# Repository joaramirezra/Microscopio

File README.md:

# Sistema de conteo de minerales para microscopio 

El siguiente repositorio cuenta con la informacion necesaria para ejecutar un sistema de conteo de minerales de manera semi-automatica haciendo uso de un microscopio, para ello es necesario poseer los siguientes componentes :

 - Computador con Linux,Windows o mac (Soporte unicamente para los dos primeros )
 - Carro de conteo automatico de puntos (Opcional ,Mas informacion proximente)
 - Dispositivo de comunicacion entre el carro de conteo y el PC (opcional)

El sistema de funcionamiento cuenta con una interfaz de usuario como se muestra a continuacion 

En ella podemos observar 5 secciones :

 1. Interfaz de conexion con dispositivo fisico
 2. Interfaz para agregar nuevas conbinaciones mineral y conjunto de letras
 3. Interfaz para agregar/borrar minerales al conteo.
 4. Resumen de minerales recientemente agregados
 5. Graficas del total de elementos agregados
 
Esta secciones permiten al usuario interactuar con el dispositivo fisico (si se posee) de tal manera que a medida que se van agregando minerales al conteo, estos de manera automatica se actualizan en la interfaz de usuario a medida que la seccion delgada se mueve de manera automatica 

## Instalación 

El proceso de instalaccion consiste en la correcta instalacion de las siguientes dependencias 
 - [python 3.6 o superior](https://www.python.org/downloads/)
    - [pyQT5](https://pypi.org/project/PyQt5/)
    - [pySerial](https://pyserial.readthedocs.io/en/latest/pyserial.html#installation)
  
Ademas de la  instalacion de las dependencias se recomienda utilizar un programa para detectar los puertos este puede ser :
- [Arduino](https://www.arduino.cc/en/software)
- [PuTTY](https://www.putty.org/)
- ó cualquiera a elección 

### checkeo requetimientos ( integridad instalacion )

Una vez instaladas las dependencias, entrar al directorio :

```
./pruebas/instalacion/
```

Alli encontrara el scrip llamado `test.py` , al ejecutarse debera obtener una respuesta como la siguiente : 

``` 
Dependencias correctamente instaladas
```

## Puesta en marcha (omitir este paso si no se posee el carro de secciones delgadas)

Para la correcta deteccion del puerto se recomienda seguir con los siguientes paso :
 1. Conexion previa : la conexion se debe realizar como se muestra en el siguiente diagrama

  alli se debe conectar el dispositivo a una fuente de voltaje de 120 Vac (toma corriente en Colombia), en ese instante debe encender una luz led como se muestra en la siguiente Imagen 

  Una vez conectado la alimentacion del dispositivo, se debe conectar un cable USB entre el computador y el dispositivo, este a su vez encendera una segunda luz en el dispositvo como se muestra en la siguiente imagen:

 2. Deteccion de puerto 
 
 Posterior a la conexion del dispositvo se debe identificar el puerto de conexion para sincronizar el dispositivo con el programa para ello acudimos al programa arduino, (o cualquiera de su preferencia) , alli presionamos
 
``` 
Herramientas/puertos
```
 Debera aparecer el nombre del puerto que se relaciona al dispositvo fisico que conectamos en el paso anterior como se muestra en la siguiente imagen (el nombre del puerto puede variar)

  - Nota 1 : En caso de usar linux se recomienda dar permisos de escritura y lectura al puerto mediante el comando `sudo chmod /dev/Nombre_del_puerto` 
  - Nota 2 : En caso de desconectar y reconectar el dispositivo asegurese que el nombre del puerto sea el mismo , en caso contrario se debe dar permisos a este nuevo puerto
  - Nota 3 : En caso de desconectar y reconectar el dispositivo asegurese que el nombre del puerto sea el mismo , en caso contrario actualizar el nombre en la interfaz grafica 
 
 3. Sincronizacion del dispositivo 
 
 Una vez se tiene el identificado el nombre del puerto y el dispositvo este correctamente conectado, se debe introducir el nombre del puerto en la casilla nombre y presionar sincronizar, esto debera 
  
7. Bibliografia 

## Agregar Nuevo combinacion mineral 

Una vez se ha sincronizado el carro con el programa es momento de iniciar a agregar los elementos a la lista de minerales que van a estar disponibles, para ello se se posee la siguientes restricciones

Es Sensible a combinaciones entre mayusculas y minisculas
longitud maxima  3 Letras
No soporta caracteres especiales ni numeros (estos ultimos estan reservados para hacer referencia a los tamaños)

### (Previo) Deteccion de puertos 

## something else 

# Colaboladores 

- [Johan Ramirez](https://github.com/joaramirezra)
- [Jurgen Krajcy](https://github.com/JurgenHK)
- Thomas Crammer

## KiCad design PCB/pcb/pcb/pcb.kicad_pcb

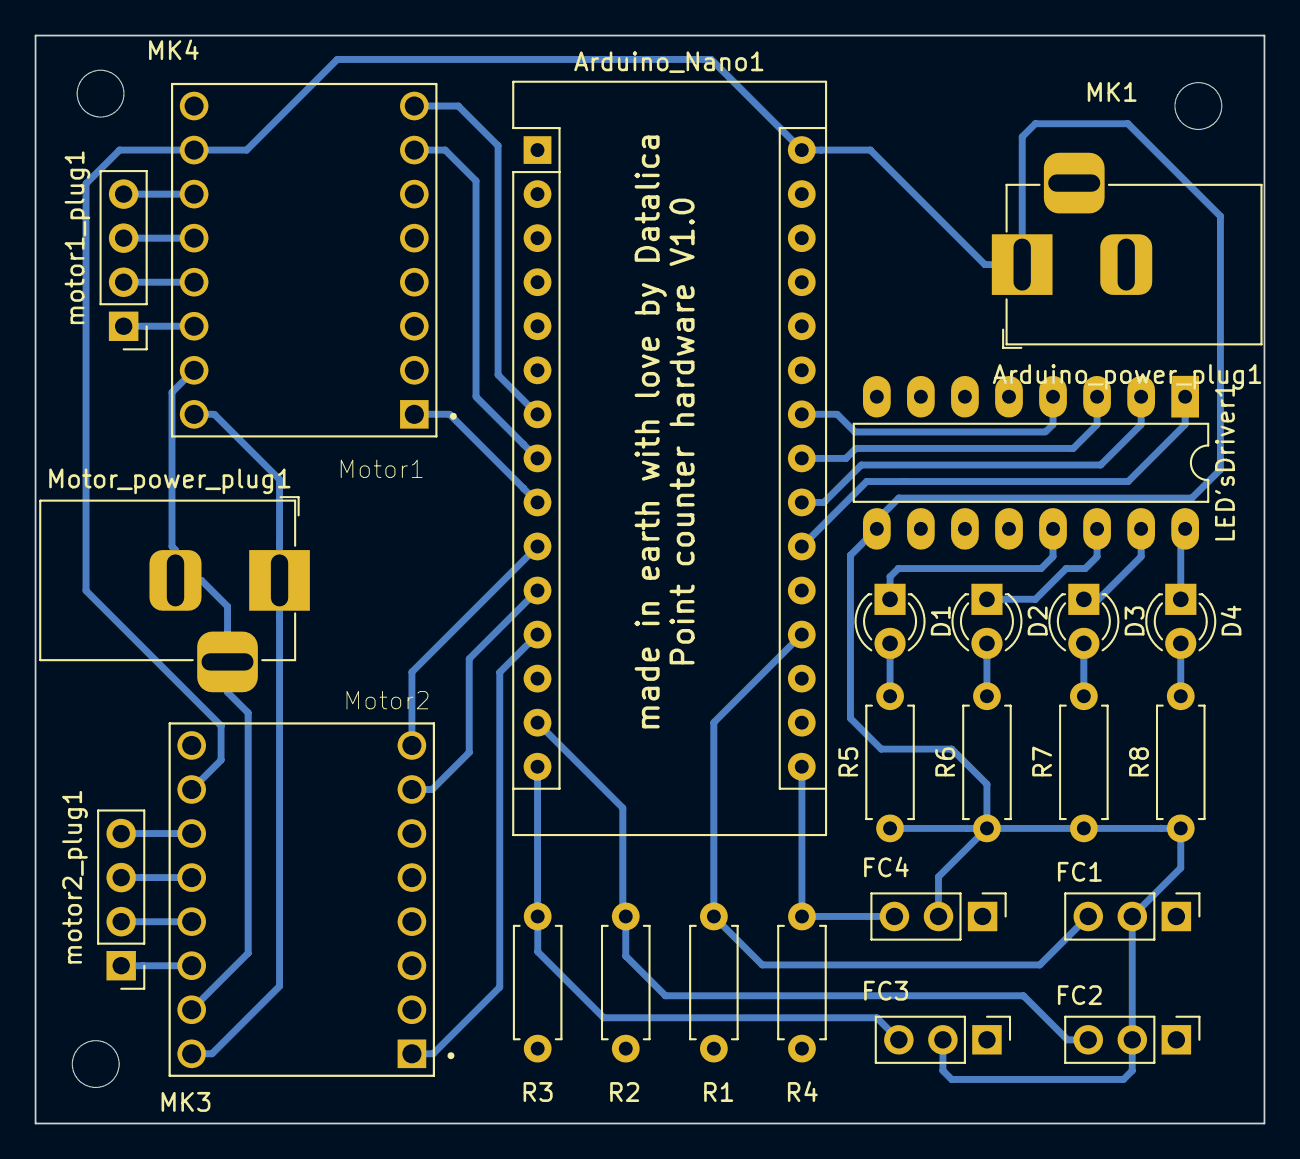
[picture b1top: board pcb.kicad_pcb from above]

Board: 2 copper layers, 70.9 x 62.7 mm, 27 parts (0 on the bottom side), 34 nets.

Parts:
Arduino_Nano1: Arduino_Nano_v2.x; Arduino_Nano
Arduino_power_plug1: Conn_01x03_Female; BarrelJack_Horizontal
D1, D2, D3, D4: LED; LED_D3.0mm_FlatTop
FC1, FC2, FC3, FC4: Conn_01x03_Female; PinHeader_1x03_P2.54mm_Vertical
LED'sDriver1: ULN2003A; DIP-16_W7.62mm_LongPads
MK1, MK3, MK4: M2.5; MountingHole_2.7mm_M2.5
Motor1, Motor2: TMC2100; IC_DRV8825_STEPPER_MOTOR_DRIVER_CARRIER
Motor_power_plug1: Conn_01x03_Female; BarrelJack_Horizontal
R1, R2, R3, R4: 10K; R_Axial_DIN0207_L6.3mm_D2.5mm_P7.62mm_Horizontal
R5, R6, R7, R8: 220; R_Axial_DIN0207_L6.3mm_D2.5mm_P7.62mm_Horizontal
motor1_plug1, motor2_plug1: Conn_01x04_Male; PinHeader_1x04_P2.54mm_Vertical

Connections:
+5V: Arduino_Nano1.30, Arduino_power_plug1.1, FC1.2, FC2.2, FC3.2, FC4.2, LED'sDriver1.9, Motor1.10, Motor2.10, R5.1, R6.1, R7.1, R8.1
Dir_motor1: Arduino_Nano1.7, Motor1.8
Dir_motor2: Arduino_Nano1.10, Motor2.8
EN_motor1: Arduino_Nano1.9, Motor1.1
EN_motor2: Arduino_Nano1.12, Motor2.1
GND: Arduino_Nano1.29, Arduino_power_plug1.2, Arduino_power_plug1.3, LED'sDriver1.8, Motor1.9, Motor2.9, R1.2, R2.2, R3.2, R4.2
GND_motor: Motor1.15, Motor2.15, Motor_power_plug1.2, Motor_power_plug1.3
LED1: Arduino_Nano1.21, LED'sDriver1.1
LED2: Arduino_Nano1.22, LED'sDriver1.2
LED3: Arduino_Nano1.23, LED'sDriver1.3
LED4: Arduino_Nano1.24, LED'sDriver1.4
Limit_switch1: Arduino_Nano1.19, FC1.3, R1.1
Limit_switch2: Arduino_Nano1.14, FC2.3, R2.1
Limit_switch3: Arduino_Nano1.15, FC3.3, R3.1
Limit_switch4: Arduino_Nano1.16, FC4.3, R4.1
unnamed: D1.2, R5.2
unnamed: D2.2, R6.2
unnamed: D3.2, R7.2
unnamed: D4.2, R8.2
S_LED1: D1.1, LED'sDriver1.13
S_LED2: D2.1, LED'sDriver1.14
S_LED3: D3.1, LED'sDriver1.15
S_LED4: D4.1, LED'sDriver1.16
Step_motor1: Arduino_Nano1.8, Motor1.7
Step_motor2: Arduino_Nano1.11, Motor2.7
Vmot_1: Motor1.16, Motor2.16, Motor_power_plug1.1
moto2_1B: Motor2.11, motor2_plug1.4
motor1_1A: Motor1.12, motor1_plug1.3
motor1_2A: Motor1.13, motor1_plug1.2
motor1_2B: Motor1.14, motor1_plug1.1
motor2_1A: Motor2.12, motor2_plug1.3
motor2_2A: Motor2.13, motor2_plug1.2
motor2_2B: Motor2.14, motor2_plug1.1
motor_1B: Motor1.11, motor1_plug1.4

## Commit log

2020-09-03 init
2020-09-03 v0.001
2020-09-04 v0.002
2020-09-06 V0.003
2020-09-07 v0.003 add class car
2020-09-07 v0.003 working on the file system control
2020-09-07 v0.003 dataflow work
2020-09-10 v0.005 interfaz optimizada
2020-09-11 V0.01 basic UI almost finish need to embed the graphs
2020-09-11 v0.005 add element
2020-09-11 v0.01 implementing dictionaries to save elements, looks to work great
2020-09-12 v01 putting the grpahs
2020-09-12 v0.02 Principal UI components working
2020-09-12 v0.02 a good day finish with all working
2020-09-13 v0.08 ux finised, also is working the add new element and is partialy the automatic counting
2020-09-14 v0.08 style working
2020-09-14 V0.09 add to table elements
2020-09-14 V0.1 element and size validation
2020-09-14 v0.15 add element to table with size
2020-09-15 v0.5 julio version
2020-09-15 v0.5 from here Julio is working in the repo
2020-09-15 New branch,Johan init
2020-09-15 V0.5 begin to work in PCB
2020-09-16 v0.6 drivers symbols created
2020-09-16 v0.6 create some milestone and fixed #1
2020-09-17 V0.7 finish the schematic that close #4
2020-09-17 V0.75 all the footprints were set
2020-09-17 V0.8 this commit close #5 also fixes #6
2020-09-17 V0.8 pcb Finished this closes #9 and closes #8
2020-09-18 V0.82 the gerbers were generated and sent to fabrication that close #7
2020-09-18 V0.85 putting bars with stepMode that is a point to solve #12
2020-09-21 V0.88 working pcb and waiting to solderin
2020-09-23 V0.86 changing color under plot line
2020-09-23 v0.9 finally put the axis labels
2020-09-23 v0.9 debug labels
2020-09-23 V0.9 code clean
2020-09-24 V 0.91 writing file line by line
2020-09-24 v0.92 point saved in a file, also the file can be reset
2020-09-24 V0.93 code to test motot
2020-09-26 V0.93 probed that code works with motors
2020-09-28 V0.93 motor with the right direr
2020-09-28 V0.94 working motor with AccelStepper library
2020-09-29 V0.94 testing comunication
2020-09-30 V0.94 motor step calculators
2020-10-01 V0.94 just some ajustments
2020-10-01 V0.95 adding 2do motor
2020-10-01 V0.95 putting switch
2020-10-02 V0.95 homing Working
2020-10-02 V0.95 serial comunication working
2020-10-02 Version 1.0
2020-10-03 V1.0 code refactor
2020-10-04 V1.01 fixing comunication
2020-10-05 V1.02 serial interruption
2020-10-05 V1.02 motors no working but the enable works
2020-10-05 V1.03 solving comunication issues
2020-10-05 V1.05 comunitication solved
2020-10-05 V1.1 home, erase and add working
2020-10-05 V1.15 settin parameters
2020-10-07 V1.1 directions on arduino
2020-10-07 V1.1 back up point
2020-10-07 V1.2 both motors working
2020-10-07 V1.4 working with interface
2020-10-07 V1.4 working interface and motors together
2020-10-08 V1.4 working need to add the counter system
2020-10-10 V1.5 new function files gives more order
2020-10-10 V1.5 close #13 , #12, #3
2020-10-11 v1.5 closes #3
2020-10-11 v1.55 working well, add the counter and closes #2
2020-10-12 V1.6 working closed #2
2020-10-12 V1.6 closes #2
2020-10-13 V1.7 this closes #5,#2
2020-10-14 v1.7 closes #12
2020-10-14 V1.7 almost finish backward automatic
2020-10-14 V1.7 working with PCB and python , have to improve file organization
2020-10-15 V1.73 working with hardarware
2020-10-15 cleanig files
2020-10-15 more cleanig
2020-10-21 V1.8 new parameters files created that closes #74
2020-10-22 V1.9 almost working with the optimization
2020-10-26 V1.9 changing logic to file format values
2020-10-28 V1.9 just need to integrate the erase and join with hardware
2020-10-29 V1.95 just a test
2020-10-29 V1.95 I need to put erase and then the progress bar
2020-10-30 V1.95 fisrt step to erase
2020-11-03 V1.99 all file system working
2020-11-03 testing johan
2020-11-03 final test
2020-11-03 V2.0 working well , for future version i need to connect with hardware
2020-11-03 V2.001 working and given
2020-11-20 V3.01 Adding new features
2020-12-16 V3.01
